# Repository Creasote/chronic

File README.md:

# chronic
Chronic project resources

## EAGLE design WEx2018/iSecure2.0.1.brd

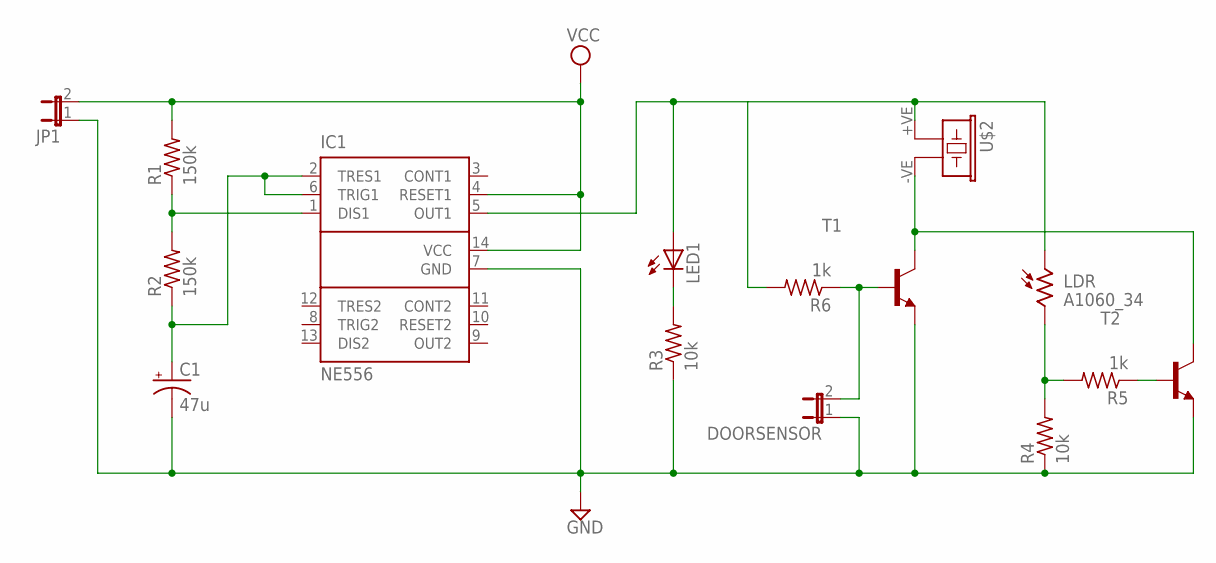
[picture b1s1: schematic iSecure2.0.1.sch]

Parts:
C1: 47u; TT5D6
DOORSENSOR: JP1E; JP1
IC1: NE556; DIL14
JP1: JP1E; JP1
LDR: A1060_34; T0-46-A10XX
LED1: LED5MM
R1, R2: 150k; 0309/12
R3, R4: 10k; 0309/12
R5, R6: 1k; 0309/12
T1, T2: 2N5550-NPN-TO92-CBE; TO92-CBE
U$2: BUZZER_AI-1440-TWTBUZZER_POLARISED; DIP762W70P0L1380H750Q2B

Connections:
GND: C1.-, DOORSENSOR.1, IC1.7 (GND), JP1.1, R3.1, R4.1, T1.E, T2.E
unnamed: IC1.1 (DIS1), R1.1, R2.2
unnamed: C1.+, IC1.2 (TRES1), IC1.6 (TRIG1), R2.1
unnamed: LED1.K (C), R3.2
unnamed: IC1.5 (OUT1), LDR.1, LED1.A, R6.2, U$2.+VE (1)
unnamed: T1.C, T2.C, U$2.-VE (2)
unnamed: DOORSENSOR.2, R6.1, T1.B
unnamed: LDR.2, R4.2, R5.2
unnamed: R5.1, T2.B
VCC: IC1.4 (RESET1), IC1.14 (VCC), JP1.2, R1.2

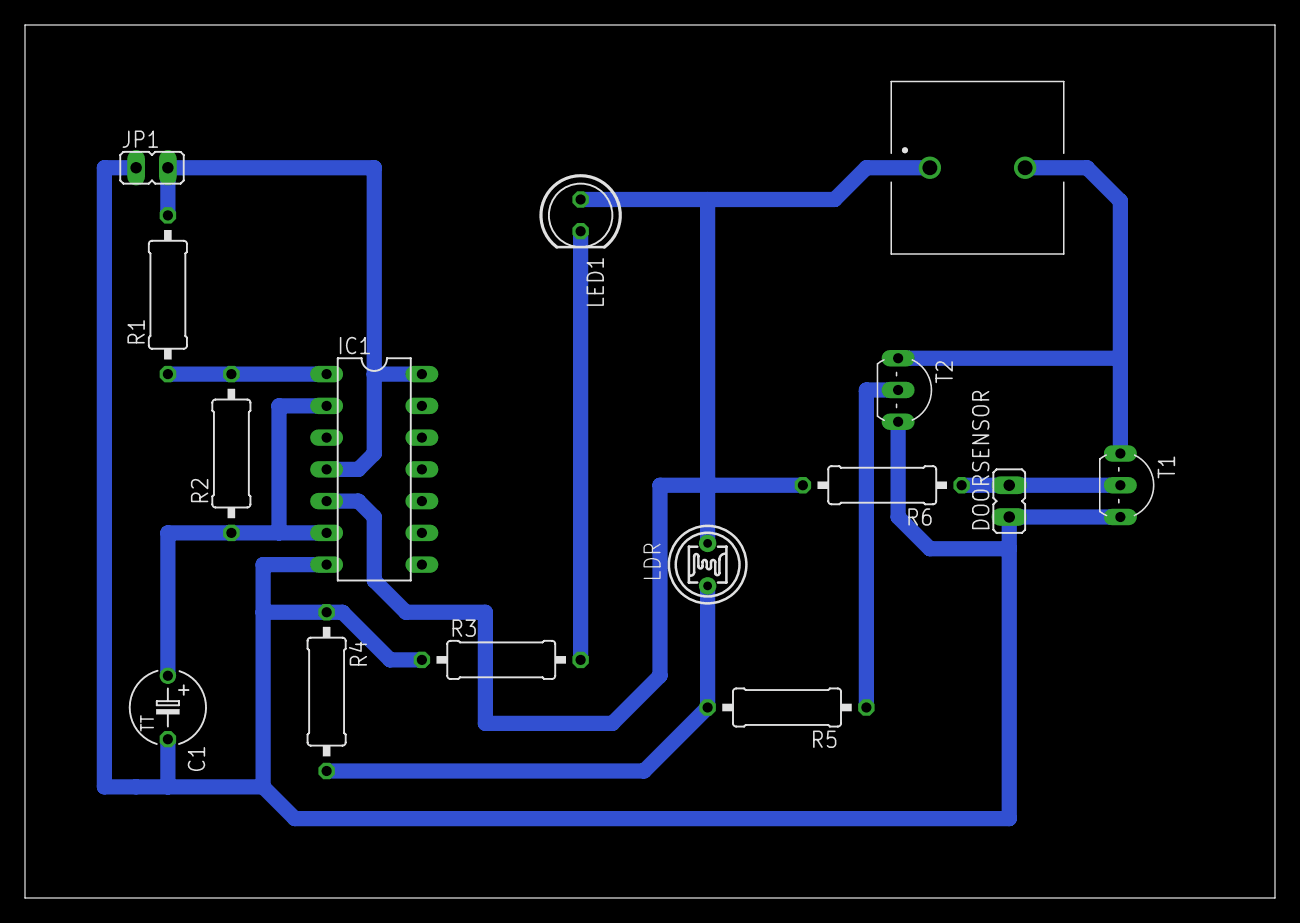
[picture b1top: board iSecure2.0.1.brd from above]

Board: 2 copper layers, 100.0 x 69.8 mm, 15 parts (0 on the bottom side), 10 nets.

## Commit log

2018-10-09 Revised latest board for milling
    2018.10.10
